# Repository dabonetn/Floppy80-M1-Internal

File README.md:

# Floppy 80 for the TRS-80 Model I - Internal Version

This is my take on the PCB for the Floppy80-M1.
It's a internal version that plugs into the Z80 socket.

I've made no changes to the firmware or docs from the source github project.  
If you try my boards and have issues,  

#**DON'T GO COMPLANING to MichaelM4.**

Please open a issue here.

Board version 1.45 has been built and tested.
Works with my Level 2 Model One.

WILL NOT FIT CORRECTLY WITH THE CPU IN A SOCKET!!!!!

AGAIN

WILL NOT FIT CORRECTLY WITH THE CPU IN A SOCKET!!!!!

This is very similar to what happens when using a Sprinter II clone, it does fit, but bends the board.

The board requires you to remove the CPU, and install the board into place.
It also requires a jumper wire from the via located on pin 2 of the edge connector. (Sysres* signal)
I highly recommend a microsd extension to mount the card outside of your case.
I have used it with a 18" (48cm) MicroSD Extension Cable from Aliexpress.

Build notes.
For the pin headers, I snip the headers that go under the cpu flush with the board and then solder them, it allows a much closer fit for the cpu.
(If you have a junk board, use that to get the length correct, so you don't nick your board with the flush cutters)
For the sysres header, if you are using a pin header, use a 90 degree header mounted on the underside of the board. Mounting on the top hits the bottom case.

JLCPCB Gerbers are under the Production directory.

BOM

Qty 4 - SN74LVC245APWR (Tssop-20)  
Qty 1 - SN74LS32 SOIC or SOP16 Footprint.  
Qty 5 - 0805 1k Resistor  
Qty 1 - 0805 100 Ohm Resistor  
Qty 6 - 0805 .1uf Capacitor  
Qty 2 - FDV301N, SSM3K324R, or 2N7002 Mosfets.  
Qty 1 - SS14 Diode  
Qty 1 - LED (5mm 3.3v compatible.) or you can substitue a 2.54 header to locate the led elsewhere.  
Qty 1 - MSD-1-A MicroSD Card Slot.  
Qty 1 - Right angle pin header, and wire for the sysres* signal from pin 2 of the edge connector.  

This is not a beginners soldering project, the ics are very small.

Here are some pics.

On this picture you can see the only flying header needed. 
Just solder a wire from here to the SYSRES* connector.

(This is the end of my changes to the readme.md)

## Features

The Floppy-80 is a Hardware and software solution that emulates 
the following features of the Expansion Interface
- A Floppy Disc controller
  - supports 3 floppy drives
  - single and double-density
  - single and double-sided
  - up to 90 cylinders
  - DMK disk format supported
- 32k RAM expansion (optional)
- 40Hz RTC interrupt generation

Additionally, the following features are provided:
- A Hard Disk Controller (optional)
  - supports up to 2 hard drives
  - Uses same image format as FreHD
- Wait State Generation (optional)
- Software Debugging Interface

An SD card is required to store disk images and configuration data

## Hardware

The Floppy-80 consists of a board that connects to the Model-1 expansion edge connector.
The board contains an SD card socket to provide disk images and a
Raspberry Pi Pico 2 microcontroller which does the emulation

[Building and testing](HARDWARE.md) the board is covered separately.

## Software

The software provided includes 2 main components
* Firmware running on Raspberry Pi, that provides the emulation
* FDC Utility (TRS DOS, and CPM) running on TRS-80 for emulator control

See the separate [Software Build Guide](BUILDING.md) for details on 
building the Floppy-80 software

## User Guide

For User Instructions please see the separate [User Guide](USER-GUIDE.md)

## Credits

## Resources

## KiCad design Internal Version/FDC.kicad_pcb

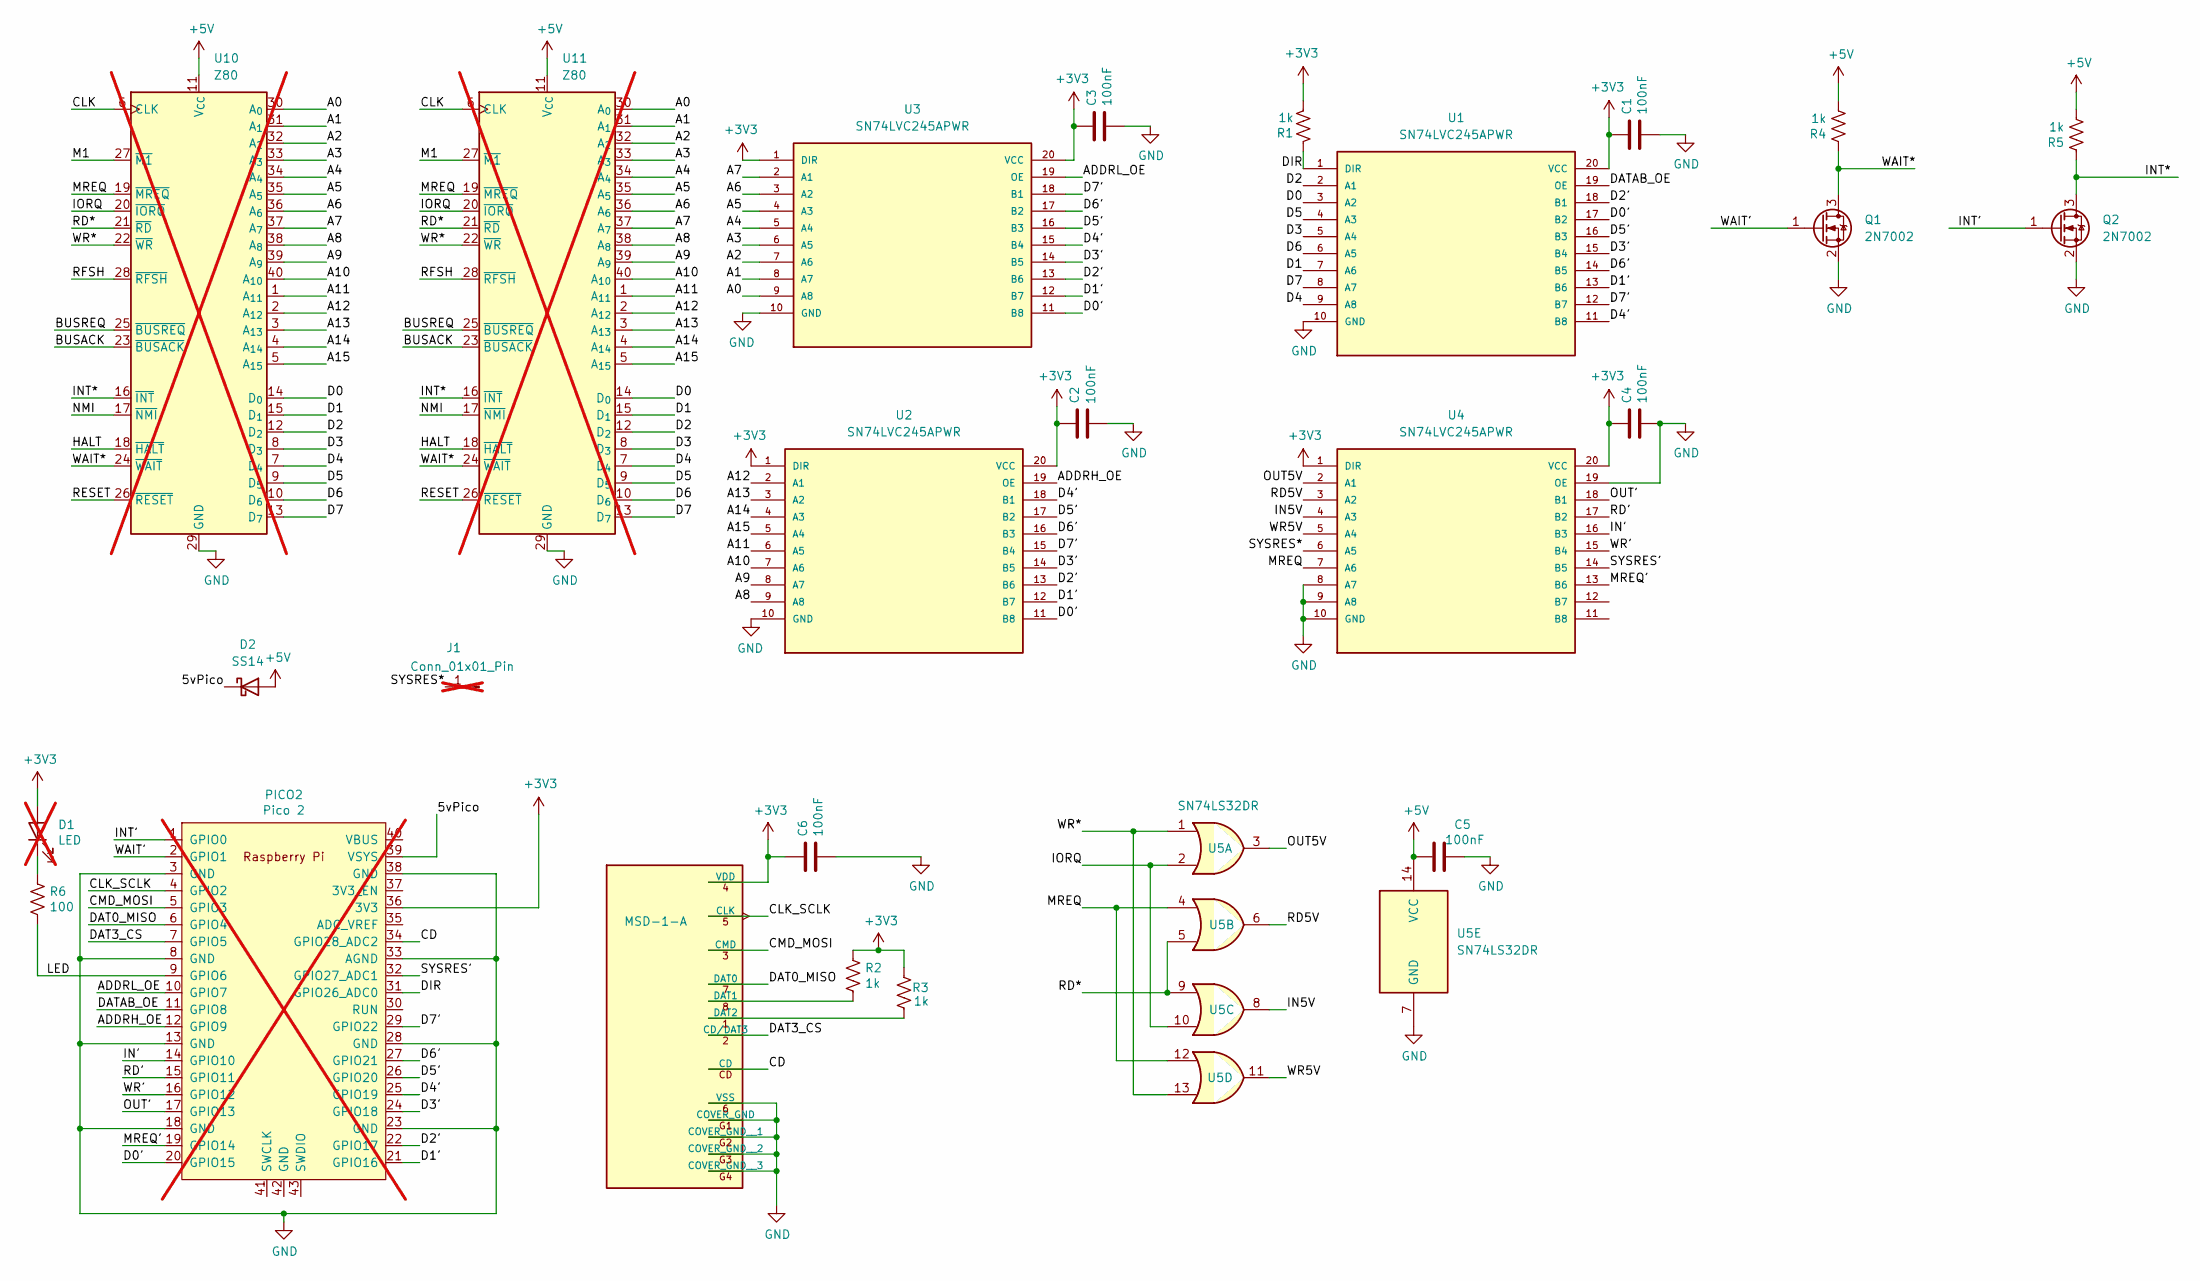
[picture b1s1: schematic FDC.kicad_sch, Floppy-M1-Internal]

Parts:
C1, C2, C3, C4, C5, C6: 100nF; C_0805_2012Metric_Pad1.18x1.45mm_HandSolder; LCSC Part # C49678
D1: LED; LED_D5.0mm; Digikey 754-1519-1-ND; not fitted
D2: SS14; D_SMA; LCSC Part # C2480
J1: Conn_01x01_Pin; PinHeader_1x01_P2.54mm_Vertical; not fitted
PICO2: Pico 2; RaspberryPi_Pico_SMD; Digikey 2648-SC1631CT-ND; not fitted
Q1, Q2: 2N7002; SOT-23_Handsoldering; LCSC Part # C65189
R1, R2, R3, R4, R5: 1k; R_0805_2012Metric_Pad1.20x1.40mm_HandSolder; Digikey A106056CT-ND
R6: 100; R_0805_2012Metric_Pad1.20x1.40mm_HandSolder; Digikey RMCF0805FT100RCT-ND
SD1: MSD-1-A; CUI_MSD-1-A; LCSC Part # C20619272
U1, U2, U3, U4: SN74LVC245APWR; TSSOP-20_4.4x6.5mm_P0.65mm; LCSC Part # C7848
U5: SN74LS32DR; SO-14_SOIC-SOP
U10, U11: Z80; DIP-40_W15.24mm; not fitted

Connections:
+3V3: C1.1, C2.1, C3.1, C4.1, C6.1, D1.2 (A), PICO2.36 (3V3), R1.2, R2.1, R3.2, SD1.4 (VDD), U1.20 (VCC), U2.1 (DIR), U2.20 (VCC), U3.1 (DIR), U3.20 (VCC), U4.1 (DIR), U4.20 (VCC); also elsewhere on the board
+5V: C5.1, D2.2 (A), R4.2, R5.2, U5.14 (VCC), U10.11 (V_{CC}), U11.11 (V_{CC})
/5vPico: D2.1 (K), PICO2.39 (VSYS)
/A0: U3.9 (A8), U10.30 (A_{0}), U11.30 (A_{0})
/A1: U3.8 (A7), U10.31 (A_{1}), U11.31 (A_{1})
/A2: U3.7 (A6), U10.32 (A_{2}), U11.32 (A_{2})
/A3: U3.6 (A5), U10.33 (A_{3}), U11.33 (A_{3})
/A4: U3.5 (A4), U10.34 (A_{4}), U11.34 (A_{4})
/A5: U3.4 (A3), U10.35 (A_{5}), U11.35 (A_{5})
/A6: U3.3 (A2), U10.36 (A_{6}), U11.36 (A_{6})
/A7: U3.2 (A1), U10.37 (A_{7}), U11.37 (A_{7})
/A8: U2.9 (A8), U10.38 (A_{8}), U11.38 (A_{8})
/A9: U2.8 (A7), U10.39 (A_{9}), U11.39 (A_{9})
/A10: U2.7 (A6), U10.40 (A_{10}), U11.40 (A_{10})
/A11: U2.6 (A5), U10.1 (A_{11}), U11.1 (A_{11})
/A12: U2.2 (A1), U10.2 (A_{12}), U11.2 (A_{12})
/A13: U2.3 (A2), U10.3 (A_{13}), U11.3 (A_{13})
/A14: U2.4 (A3), U10.4 (A_{14}), U11.4 (A_{14})
/A15: U2.5 (A4), U10.5 (A_{15}), U11.5 (A_{15})
/ADDRH_OE: PICO2.12 (GPIO9), U2.19 (OE)
/ADDRL_OE: PICO2.10 (GPIO7), U3.19 (OE)
/BUSACK: U10.23 (~BUSACK), U11.23 (~BUSACK)
/BUSREQ: U10.25 (~BUSREQ), U11.25 (~BUSREQ)
/CD: PICO2.34 (GPIO28_ADC2), SD1.CD
/CLK: U10.6 (CLK), U11.6 (CLK)
/CLK_SCLK: PICO2.4 (GPIO2), SD1.5 (CLK)
/CMD_MOSI: PICO2.5 (GPIO3), SD1.3 (CMD)
/D0: U1.3 (A2), U10.14 (D_{0}), U11.14 (D_{0})
/D0': PICO2.20 (GPIO15), U1.17 (B2), U2.11 (B8), U3.11 (B8)
/D1: U1.7 (A6), U10.15 (D_{1}), U11.15 (D_{1})
/D1': PICO2.21 (GPIO16), U1.13 (B6), U2.12 (B7), U3.12 (B7)
/D2: U1.2 (A1), U10.12 (D_{2}), U11.12 (D_{2})
/D2': PICO2.22 (GPIO17), U1.18 (B1), U2.13 (B6), U3.13 (B6)
/D3: U1.5 (A4), U10.8 (D_{3}), U11.8 (D_{3})
/D3': PICO2.24 (GPIO18), U1.15 (B4), U2.14 (B5), U3.14 (B5)
/D4: U1.9 (A8), U10.7 (D_{4}), U11.7 (D_{4})
/D4': PICO2.25 (GPIO19), U1.11 (B8), U2.18 (B1), U3.15 (B4)
/D5: U1.4 (A3), U10.9 (D_{5}), U11.9 (D_{5})
/D5': PICO2.26 (GPIO20), U1.16 (B3), U2.17 (B2), U3.16 (B3)
/D6: U1.6 (A5), U10.10 (D_{6}), U11.10 (D_{6})
/D6': PICO2.27 (GPIO21), U1.14 (B5), U2.16 (B3), U3.17 (B2)
/D7: U1.8 (A7), U10.13 (D_{7}), U11.13 (D_{7})
/D7': PICO2.29 (GPIO22), U1.12 (B7), U2.15 (B4), U3.18 (B1)
/DAT0_MISO: PICO2.6 (GPIO4), SD1.7 (DAT0)
/DAT3_CS: PICO2.7 (GPIO5), SD1.2 (CD/DAT3)
/DATAB_OE: PICO2.11 (GPIO8), U1.19 (OE)
/DIR: PICO2.31 (GPIO26_ADC0), R1.1, U1.1 (DIR)
/HALT: U10.18 (~HALT), U11.18 (~HALT)
/IN5V: U4.4 (A3), U5.8
/IN': PICO2.14 (GPIO10), U4.16 (B3)
/INT': PICO2.1 (GPIO0), Q2.1 (G)
/INT*: Q2.3 (D), R5.1, U10.16 (~INT), U11.16 (~INT)
/IORQ: U5.2, U5.10, U10.20 (~IORQ), U11.20 (~IORQ)
/LED: PICO2.9 (GPIO6), R6.2
/M1: U10.27 (~M1), U11.27 (~M1)
/MREQ: U4.7 (A6), U5.4, U5.12, U10.19 (~MREQ), U11.19 (~MREQ)
/MREQ': PICO2.19 (GPIO14), U4.13 (B6)
/NMI: U10.17 (~NMI), U11.17 (~NMI)
/OUT5V: U4.2 (A1), U5.3
/OUT': PICO2.17 (GPIO13), U4.18 (B1)
/RD5V: U4.3 (A2), U5.6
/RD': PICO2.15 (GPIO11), U4.17 (B2)
/RD*: U5.5, U5.9, U10.21 (~RD), U11.21 (~RD)
/RESET: U10.26 (~RESET), U11.26 (~RESET)
/RFSH: U10.28 (~RFSH), U11.28 (~RFSH)
/SYSRES': PICO2.32 (GPIO27_ADC1), U4.14 (B5)
/SYSRES*: J1.1 (Pin_1_1), U4.6 (A5)
/WAIT': PICO2.2 (GPIO1), Q1.1 (G)
/WAIT*: Q1.3 (D), R4.1, U10.24 (~WAIT), U11.24 (~WAIT)
/WR5V: U4.5 (A4), U5.11
/WR': PICO2.16 (GPIO12), U4.15 (B4)
/WR*: U5.1, U5.13, U10.22 (~WR), U11.22 (~WR)
GND: C1.2, C2.2, C3.2, C4.2, C5.2, C6.2, PICO2.3 (GND), PICO2.8 (GND), PICO2.13 (GND), PICO2.18 (GND), PICO2.23 (GND), PICO2.28 (GND), PICO2.33 (AGND), PICO2.38 (GND), Q1.2 (S), Q2.2 (S), SD1.6 (VSS), SD1.G1 (COVER_GND), SD1.G2 (COVER_GND__1), SD1.G3 (COVER_GND__2), SD1.G4 (COVER_GND__3), U1.10 (GND), U2.10 (GND), U3.10 (GND), U4.8 (A7), U4.9 (A8), U4.10 (GND), U4.19 (OE), U5.7 (GND), U10.29 (GND), U11.29 (GND); also elsewhere on the board
unnamed: D1.1 (K), R6.1
unnamed: R2.2, SD1.8 (DAT1)
unnamed: R3.1, SD1.1 (DAT2)

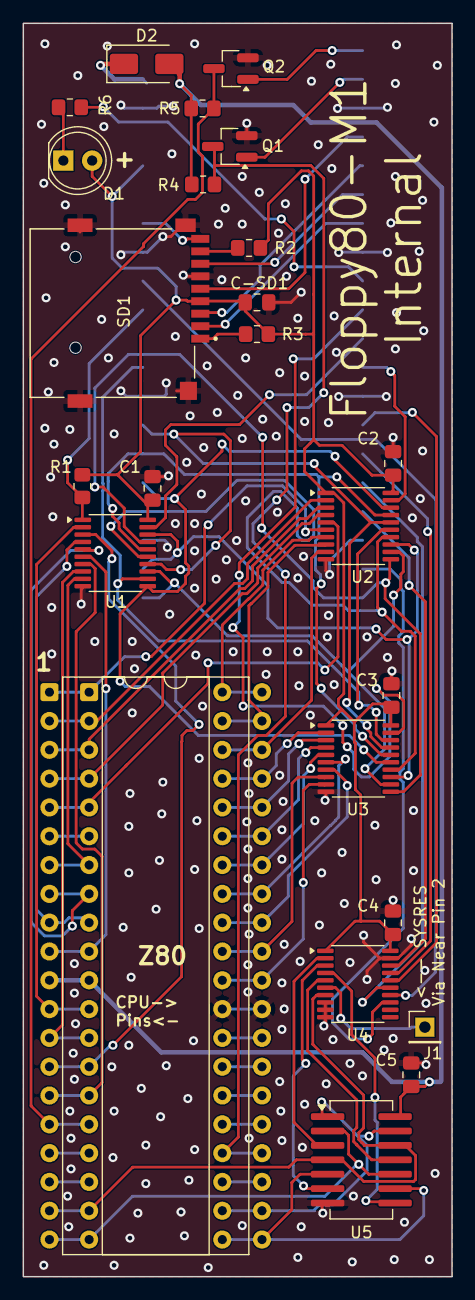
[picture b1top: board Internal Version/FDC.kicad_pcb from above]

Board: 2 copper layers, 37.8 x 110.5 mm, 26 parts (1 on the bottom side), 76 nets.

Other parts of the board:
C-SD1: 100nF; C_0805_2012Metric_Pad1.18x1.45mm_HandSolder

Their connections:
+3V3: C-SD1.1; also elsewhere on the board
GND: C-SD1.2; also elsewhere on the board

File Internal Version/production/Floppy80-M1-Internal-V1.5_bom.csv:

Designator,Footprint,Quantity,Value,LCSC Part #
"C1, C2, C3, C4, C5, C6",0805,6,100nF,C49678
D2,D_SMA,1,SS14,C2480
"Q1, Q2",SOT-23_Handsoldering,2,2N7002,C65189
"R1, R2, R3, R4, R5",0805,5,1k,C2907232
R6,0805,1,100,C105577
SD1,CUI_MSD-1-A,1,MSD-1-A,C20619272
"U1, U2, U3, U4",TSSOP-20_4.4x6.5mm_P0.65mm,4,SN74LVC245APWR,C7848
U5,SO-14_SOIC-SOP,1,SN74LS32DR,

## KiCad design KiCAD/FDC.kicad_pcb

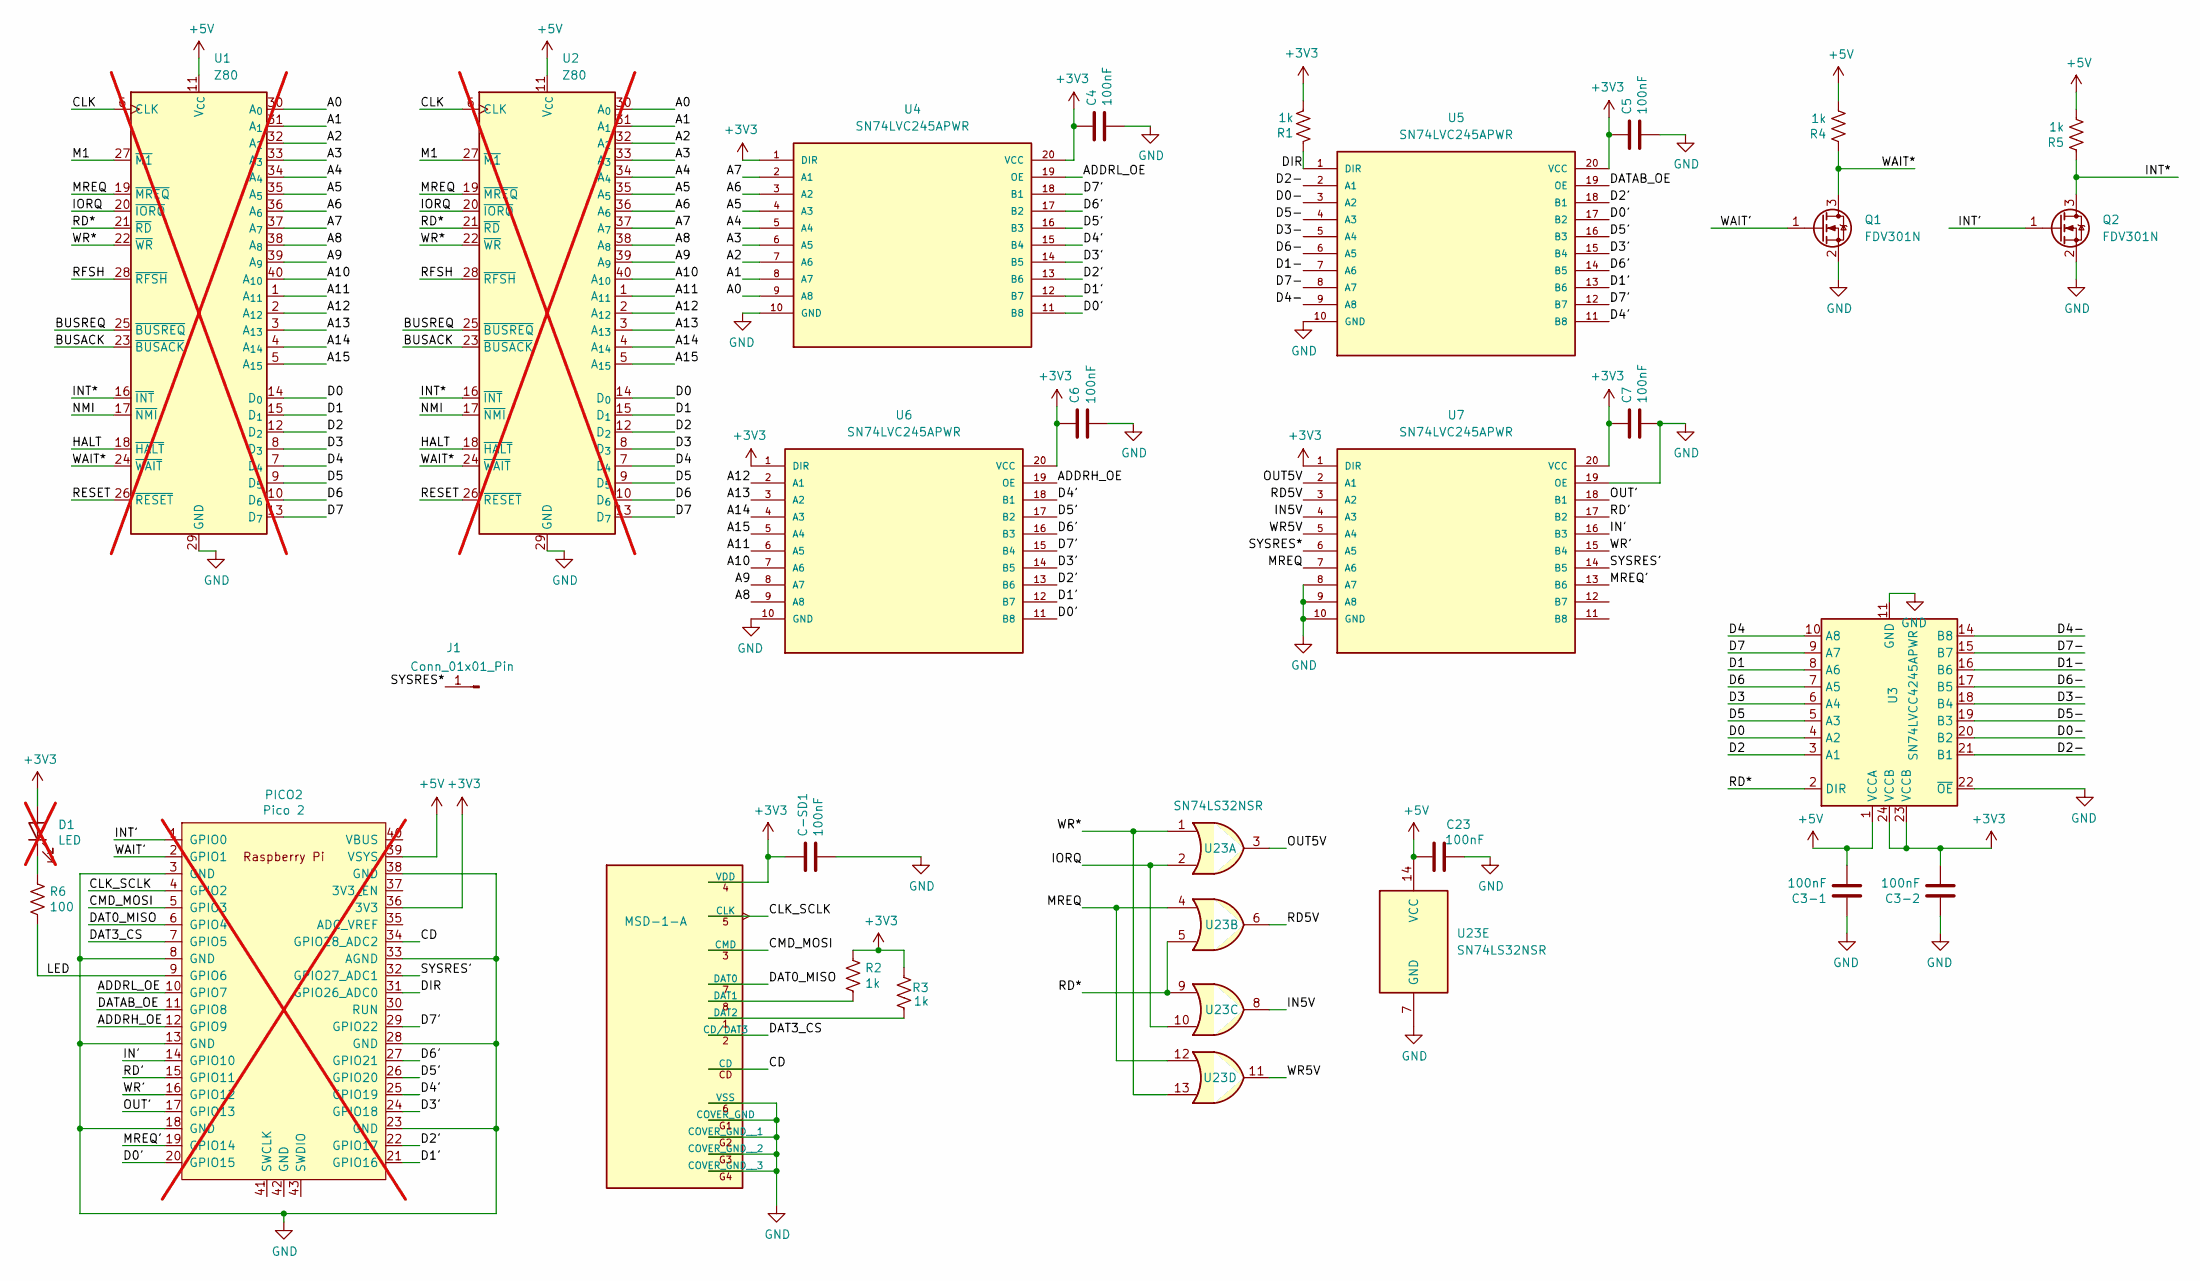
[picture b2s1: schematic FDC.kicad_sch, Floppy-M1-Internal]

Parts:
C3-1, C3-2, C4, C5, C6, C7, C23: 100nF; C_0805_2012Metric_Pad1.18x1.45mm_HandSolder; Digikey 732-8080-1-ND
C-SD1: 100nF; C_0805_2012Metric_Pad1.18x1.45mm_HandSolder; Digikey 732-8080-1-ND
D1: LED; LED_D5.0mm; Digikey 754-1519-1-ND; not fitted
J1: Conn_01x01_Pin; PinHeader_1x01_P2.54mm_Vertical
PICO2: Pico 2; RaspberryPi_Pico_SMD; Digikey 2648-SC1631CT-ND; not fitted
Q1, Q2: FDV301N; SOT-23_Handsoldering; Digikey FDV301NCT-ND
R1, R2, R3, R4, R5: 1k; R_0805_2012Metric_Pad1.20x1.40mm_HandSolder; Digikey A106056CT-ND
R6: 100; R_0805_2012Metric_Pad1.20x1.40mm_HandSolder; Digikey RMCF0805FT100RCT-ND
SD1: MSD-1-A; CUI_MSD-1-A; LCSC Part # C20619272
U1, U2: Z80; DIP-40_W15.24mm; not fitted
U3: SN74LVCC4245APWR; TSSOP-24_4.4x7.8mm_P0.65mm; Digikey 296-26634-1-ND
U4, U5, U6, U7: SN74LVC245APWR; TSSOP-20_4.4x6.5mm_P0.65mm; LCSC Part # C6082
U23: SN74LS32NSR; SOIC-14_3.9x8.7mm_P1.27mm

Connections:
+3V3: C3-2.2, C4.1, C5.1, C6.1, C7.1, C-SD1.1, D1.2 (A), PICO2.36 (3V3), R1.2, R2.1, R3.2, SD1.4 (VDD), U3.23 (VCCB), U3.24 (VCCB), U4.1 (DIR), U4.20 (VCC), U5.20 (VCC), U6.1 (DIR), U6.20 (VCC), U7.1 (DIR), U7.20 (VCC)
+5V: C3-1.2, C23.1, PICO2.39 (VSYS), R4.2, R5.2, U1.11 (V_{CC}), U2.11 (V_{CC}), U3.1 (VCCA), U23.14 (VCC)
/A0: U1.30 (A_{0}), U2.30 (A_{0}), U4.9 (A8)
/A1: U1.31 (A_{1}), U2.31 (A_{1}), U4.8 (A7)
/A2: U1.32 (A_{2}), U2.32 (A_{2}), U4.7 (A6)
/A3: U1.33 (A_{3}), U2.33 (A_{3}), U4.6 (A5)
/A4: U1.34 (A_{4}), U2.34 (A_{4}), U4.5 (A4)
/A5: U1.35 (A_{5}), U2.35 (A_{5}), U4.4 (A3)
/A6: U1.36 (A_{6}), U2.36 (A_{6}), U4.3 (A2)
/A7: U1.37 (A_{7}), U2.37 (A_{7}), U4.2 (A1)
/A8: U1.38 (A_{8}), U2.38 (A_{8}), U6.9 (A8)
/A9: U1.39 (A_{9}), U2.39 (A_{9}), U6.8 (A7)
/A10: U1.40 (A_{10}), U2.40 (A_{10}), U6.7 (A6)
/A11: U1.1 (A_{11}), U2.1 (A_{11}), U6.6 (A5)
/A12: U1.2 (A_{12}), U2.2 (A_{12}), U6.2 (A1)
/A13: U1.3 (A_{13}), U2.3 (A_{13}), U6.3 (A2)
/A14: U1.4 (A_{14}), U2.4 (A_{14}), U6.4 (A3)
/A15: U1.5 (A_{15}), U2.5 (A_{15}), U6.5 (A4)
/ADDRH_OE: PICO2.12 (GPIO9), U6.19 (OE)
/ADDRL_OE: PICO2.10 (GPIO7), U4.19 (OE)
/BUSACK: U1.23 (~BUSACK), U2.23 (~BUSACK)
/BUSREQ: U1.25 (~BUSREQ), U2.25 (~BUSREQ)
/CD: PICO2.34 (GPIO28_ADC2), SD1.CD
/CLK: U1.6 (CLK), U2.6 (CLK)
/CLK_SCLK: PICO2.4 (GPIO2), SD1.5 (CLK)
/CMD_MOSI: PICO2.5 (GPIO3), SD1.3 (CMD)
/D0: U1.14 (D_{0}), U2.14 (D_{0}), U3.4 (A2)
/D0': PICO2.20 (GPIO15), U4.11 (B8), U5.17 (B2), U6.11 (B8)
/D0-: U3.20 (B2), U5.3 (A2)
/D1: U1.15 (D_{1}), U2.15 (D_{1}), U3.8 (A6)
/D1': PICO2.21 (GPIO16), U4.12 (B7), U5.13 (B6), U6.12 (B7)
/D1-: U3.16 (B6), U5.7 (A6)
/D2: U1.12 (D_{2}), U2.12 (D_{2}), U3.3 (A1)
/D2': PICO2.22 (GPIO17), U4.13 (B6), U5.18 (B1), U6.13 (B6)
/D2-: U3.21 (B1), U5.2 (A1)
/D3: U1.8 (D_{3}), U2.8 (D_{3}), U3.6 (A4)
/D3': PICO2.24 (GPIO18), U4.14 (B5), U5.15 (B4), U6.14 (B5)
/D3-: U3.18 (B4), U5.5 (A4)
/D4: U1.7 (D_{4}), U2.7 (D_{4}), U3.10 (A8)
/D4': PICO2.25 (GPIO19), U4.15 (B4), U5.11 (B8), U6.18 (B1)
/D4-: U3.14 (B8), U5.9 (A8)
/D5: U1.9 (D_{5}), U2.9 (D_{5}), U3.5 (A3)
/D5': PICO2.26 (GPIO20), U4.16 (B3), U5.16 (B3), U6.17 (B2)
/D5-: U3.19 (B3), U5.4 (A3)
/D6: U1.10 (D_{6}), U2.10 (D_{6}), U3.7 (A5)
/D6': PICO2.27 (GPIO21), U4.17 (B2), U5.14 (B5), U6.16 (B3)
/D6-: U3.17 (B5), U5.6 (A5)
/D7: U1.13 (D_{7}), U2.13 (D_{7}), U3.9 (A7)
/D7': PICO2.29 (GPIO22), U4.18 (B1), U5.12 (B7), U6.15 (B4)
/D7-: U3.15 (B7), U5.8 (A7)
/DAT0_MISO: PICO2.6 (GPIO4), SD1.7 (DAT0)
/DAT3_CS: PICO2.7 (GPIO5), SD1.2 (CD/DAT3)
/DATAB_OE: PICO2.11 (GPIO8), U5.19 (OE)
/DIR: PICO2.31 (GPIO26_ADC0), R1.1, U5.1 (DIR)
/HALT: U1.18 (~HALT), U2.18 (~HALT)
/IN5V: U7.4 (A3), U23.8
/IN': PICO2.14 (GPIO10), U7.16 (B3)
/INT': PICO2.1 (GPIO0), Q2.1 (G)
/INT*: Q2.3 (D), R5.1, U1.16 (~INT), U2.16 (~INT)
/IORQ: U1.20 (~IORQ), U2.20 (~IORQ), U23.2, U23.10
/LED: PICO2.9 (GPIO6), R6.2
/M1: U1.27 (~M1), U2.27 (~M1)
/MREQ: U1.19 (~MREQ), U2.19 (~MREQ), U7.7 (A6), U23.4, U23.12
/MREQ': PICO2.19 (GPIO14), U7.13 (B6)
/NMI: U1.17 (~NMI), U2.17 (~NMI)
/OUT5V: U7.2 (A1), U23.3
/OUT': PICO2.17 (GPIO13), U7.18 (B1)
/RD5V: U7.3 (A2), U23.6
/RD': PICO2.15 (GPIO11), U7.17 (B2)
/RD*: U1.21 (~RD), U2.21 (~RD), U3.2 (DIR), U23.5, U23.9
/RESET: U1.26 (~RESET), U2.26 (~RESET)
/RFSH: U1.28 (~RFSH), U2.28 (~RFSH)
/SYSRES': PICO2.32 (GPIO27_ADC1), U7.14 (B5)
/SYSRES*: J1.1 (Pin_1_1), U7.6 (A5)
/WAIT': PICO2.2 (GPIO1), Q1.1 (G)
/WAIT*: Q1.3 (D), R4.1, U1.24 (~WAIT), U2.24 (~WAIT)
/WR5V: U7.5 (A4), U23.11
/WR': PICO2.16 (GPIO12), U7.15 (B4)
/WR*: U1.22 (~WR), U2.22 (~WR), U23.1, U23.13
GND: C3-1.1, C3-2.1, C4.2, C5.2, C6.2, C7.2, C23.2, C-SD1.2, PICO2.3 (GND), PICO2.8 (GND), PICO2.13 (GND), PICO2.18 (GND), PICO2.23 (GND), PICO2.28 (GND), PICO2.33 (AGND), PICO2.38 (GND), Q1.2 (S), Q2.2 (S), SD1.6 (VSS), SD1.G1 (COVER_GND), SD1.G2 (COVER_GND__1), SD1.G3 (COVER_GND__2), SD1.G4 (COVER_GND__3), U1.29 (GND), U2.29 (GND), U3.11 (GND), U3.12 (GND), U3.13 (GND), U3.22 (~OE), U4.10 (GND), U5.10 (GND), U6.10 (GND), U7.8 (A7), U7.9 (A8), U7.10 (GND), U7.19 (OE), U23.7 (GND)
unnamed: D1.1 (K), R6.1
unnamed: R2.2, SD1.8 (DAT1)
unnamed: R3.1, SD1.1 (DAT2)

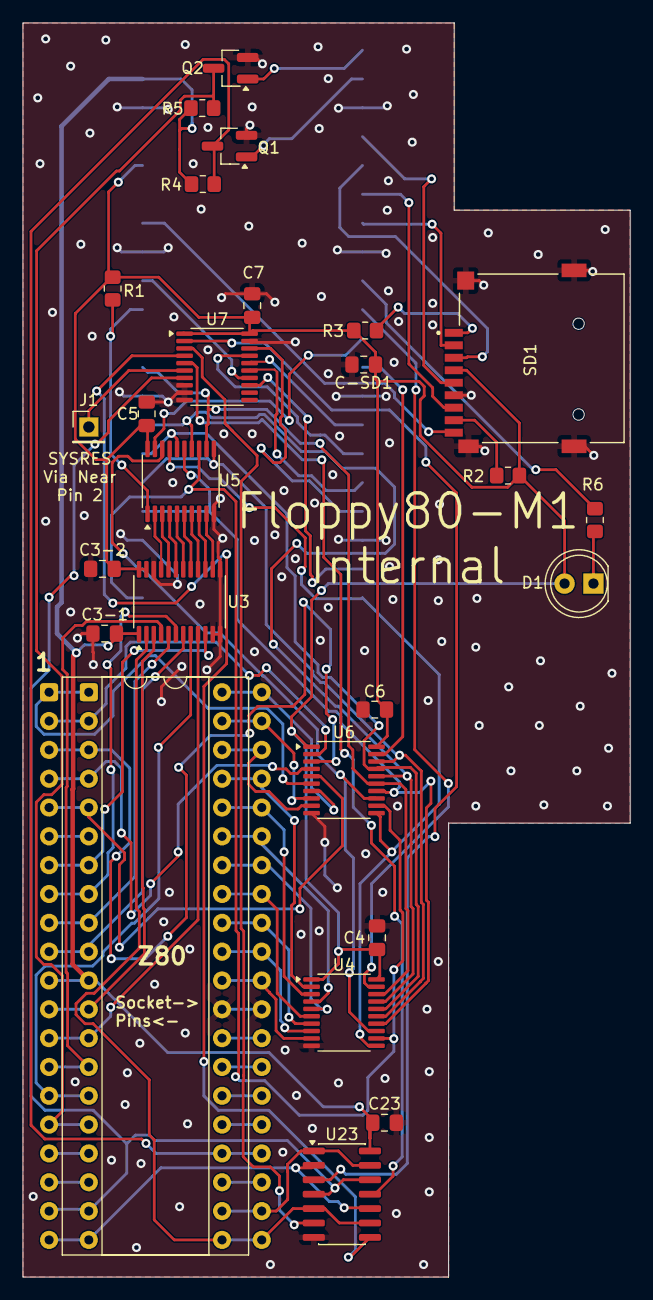
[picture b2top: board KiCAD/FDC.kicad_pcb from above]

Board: 2 copper layers, 53.5 x 110.5 mm, 28 parts (1 on the bottom side), 83 nets.

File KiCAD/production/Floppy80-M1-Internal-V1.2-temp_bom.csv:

Designator,Footprint,Quantity,Value,LCSC Part #
"C-SD1, C23, C3-1, C3-2, C4, C5, C6, C7",0805,8,100nF,C49678
J1,PinHeader_1x01_P2.54mm_Vertical,1,Conn_01x01_Pin,
"Q1, Q2",SOT-23_Handsoldering,2,FDV301N,C15310
"R1, R2, R3, R4, R5",0805,5,1k,C2907232
R6,0805,1,100,C105577
SD1,CUI_MSD-1-A,1,MSD-1-A,C20619272
U23,SOIC-14_3.9x8.7mm_P1.27mm,1,SN74LS32NSR,
U3,TSSOP-24_4.4x7.8mm_P0.65mm,1,SN74LVCC4245APWR,
"U4, U5, U6, U7",TSSOP-20_4.4x6.5mm_P0.65mm,4,SN74LVC245APWR,C6082
